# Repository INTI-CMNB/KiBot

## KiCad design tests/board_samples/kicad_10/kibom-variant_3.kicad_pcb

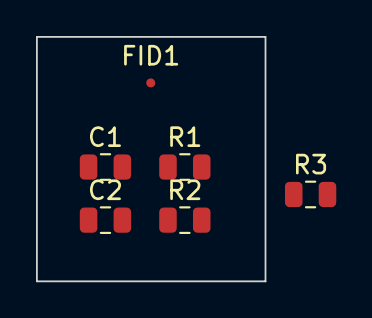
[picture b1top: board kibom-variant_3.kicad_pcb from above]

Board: 2 copper layers, 12.7 x 13.6 mm, 6 parts (0 on the bottom side), 2 nets, no tracks yet.

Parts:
C1: 1nF; C_0805_2012Metric
C2: 1000 pF; C_0805_2012Metric
FID1: Fiducial; Fiducial_0.5mm_Mask1mm
R1, R3: 1k; R_0805_2012Metric
R2: 1000; R_0805_2012Metric

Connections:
unnamed: R1.1, R3.1
unnamed: R1.2, R3.2

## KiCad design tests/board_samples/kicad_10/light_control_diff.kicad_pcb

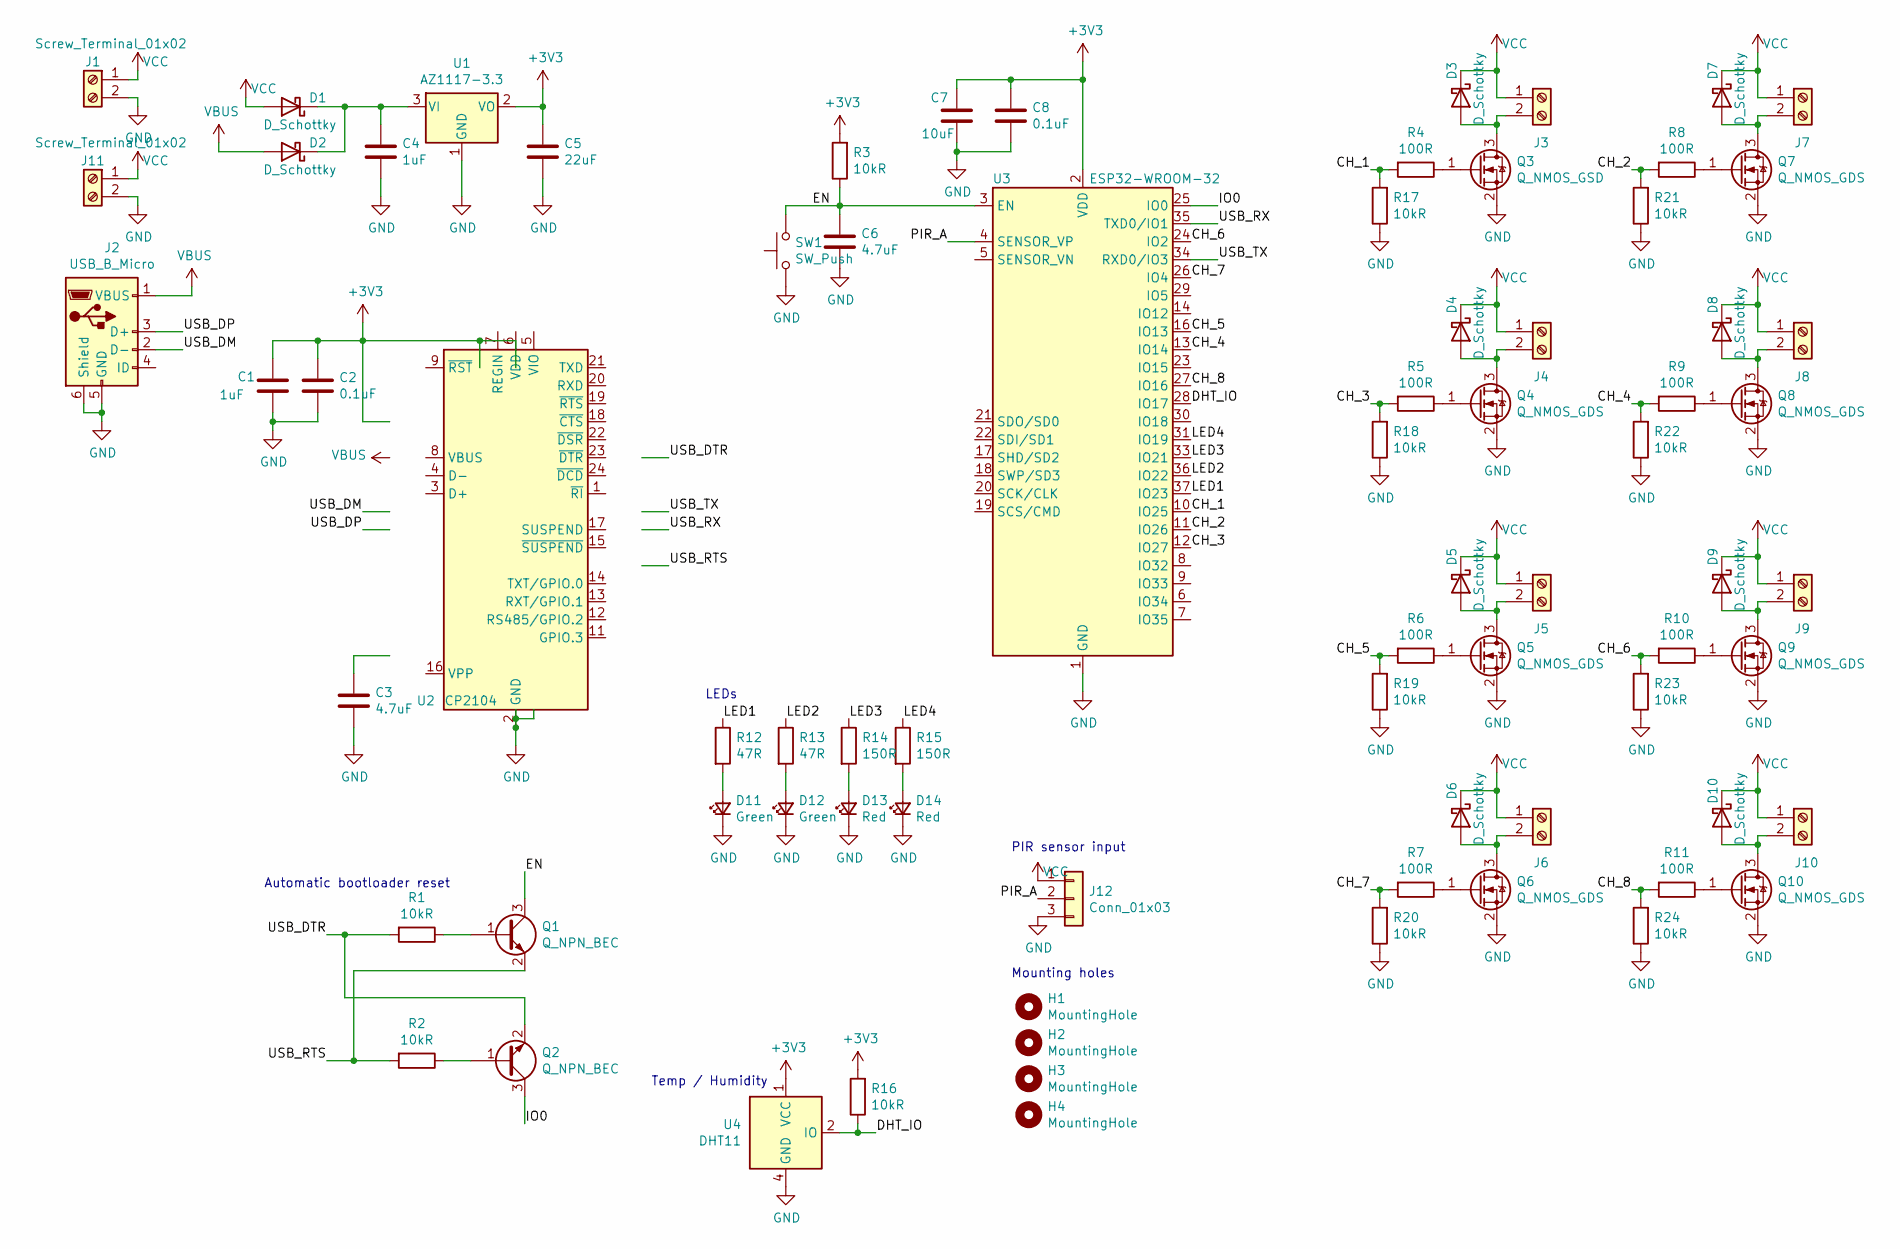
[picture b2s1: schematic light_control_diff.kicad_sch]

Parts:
C1: 1uF; R_0402_1005Metric; MPN CL05A105KA5NQNC; LCSC# C52923
C2, C8: 0.1uF; R_0402_1005Metric; MPN CL05B104KO5NNNC; LCSC# C1525
C3: 4.7uF; R_0603_1608Metric; MPN CL10A475KO8NNNC; LCSC# C19666
C4: 1uF; R_0603_1608Metric; MPN CL10A105KB8NNNC; LCSC# C15849
C5: 22uF; R_0603_1608Metric; MPN CL10A226MQ8NRNC; LCSC# C59461
C6: 4.7uF; R_0402_1005Metric; MPN CL05A475MP5NRNC; LCSC# C23733
C7: 10uF; R_0402_1005Metric; MPN CL05A106MQ5NUNC; LCSC# C15525
D1, D2, D3, D4, D5, D6, D7, D8, D9, D10: D_Schottky; D_SOD-123; MPN B5819W SL; LCSC# C8598
D11, D12: Green; LED_0603_1608Metric; MPN 19-217/GHC-YR1S2/3T; LCSC# C72043
D13, D14: Red; LED_0603_1608Metric; LCSC# C2286
H1, H2, H3, H4: MountingHole; MountingHole_3.2mm_M3
J1, J3, J4, J5, J6, J7, J8, J9, J10, J11: Screw_Terminal_01x02; TerminalBlock_Phoenix_PT-1,5-2-3.5-H_1x02_P3.50mm_Horizontal
J2: USB_B_Micro; USB_Micro-B_Molex-105017-0001
J12: Conn_01x03; JST_XH_B3B-XH-A_1x03_P2.50mm_Vertical
Q1, Q2: Q_NPN_BEC; SOT-23; MPN SS8050; LCSC# C2150
Q3: Q_NMOS_GSD; SOT-23; MPN AO3400A; LCSC# C20917
Q4, Q5, Q6, Q7, Q8, Q9, Q10: Q_NMOS_GDS; SOT-23; MPN AO3400A; LCSC# C20917
R1, R2, R3, R16, R17, R18, R19, R20, R21, R22, R23, R24: 10kR; R_0402_1005Metric; MPN 0402WGF1002TCE; LCSC# C25744
R4, R5, R6, R7, R8, R9, R10, R11: 100R; R_0402_1005Metric; MPN 0402WGF1000TCE; LCSC# C25076
R12: 47R; R_0402_1005Metric; MPN 19-217/GHC-YR1S2/3T; LCSC# C25118
R13: 47R; R_0402_1005Metric; MPN 0402WGF470JTCE; LCSC# C25118
R14, R15: 150R; R_0402_1005Metric; MPN 0402WGF1500TCE; LCSC# C25082
SW1: SW_Push; TS-1187A; MPN TS-1187A-C-D-B; LCSC# C318888
U1: AZ1117-3.3; SOT-223-3_TabPin2; MPN AZ1117CH-3.3TRG1; LCSC# C92102
U2: CP2104; QFN-24-1EP_4x4mm_P0.5mm_EP2.6x2.6mm; MPN CP2104-F03-GMR; LCSC# C47742
U3: ESP32-WROOM-32
U4: DHT11; Aosong_DHT11_5.5x12.0_P2.54mm

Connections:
+3V3: C1.1, C2.1, C5.1, C7.1, C8.1, R3.2, R16.2, U1.2 (VO), U2.5 (VIO), U2.6 (VDD), U2.7 (REGIN), U3.2 (VDD), U4.1 (VCC)
/CH_1: R4.2, R17.2, U3.10 (IO25)
/CH_2: R8.2, R21.2, U3.11 (IO26)
/CH_3: R5.2, R18.2, U3.12 (IO27)
/CH_4: R9.2, R22.2, U3.13 (IO14)
/CH_5: R6.2, R19.2, U3.16 (IO13)
/CH_6: R10.2, R23.2, U3.24 (IO2)
/CH_7: R7.2, R20.2, U3.26 (IO4)
/CH_8: R11.2, R24.2, U3.27 (IO16)
/DHT_IO: R16.1, U3.28 (IO17), U4.2 (IO)
/EN: C6.1, Q1.3 (C), R3.1, SW1.2, U3.3 (EN)
/IO0: Q2.3 (C), U3.25 (IO0)
/LED1: R12.1, U3.37 (IO23)
/LED2: R13.1, U3.36 (IO22)
/LED3: R14.1, U3.33 (IO21)
/LED4: R15.1, U3.31 (IO19)
/PIR_A: J12.2, U3.4 (SENSOR_VP)
/USB_DM: J2.2 (D-), U2.4 (D-)
/USB_DP: J2.3 (D+), U2.3 (D+)
/USB_DTR: Q2.2 (E), R1.2, U2.23 (~DTR)
/USB_RTS: Q1.2 (E), R2.2, U2.19 (~RTS)
/USB_RX: U2.20 (RXD), U3.35 (TXD0/IO1)
/USB_TX: U2.21 (TXD), U3.34 (RXD0/IO3)
GND: C1.2, C2.2, C3.2, C4.2, C5.2, C6.2, C7.2, C8.2, D11.1 (K), D12.1 (K), D13.1 (K), D14.1 (K), J1.2, J2.5 (GND), J2.6 (Shield), J11.2, J12.3, Q3.2 (S), Q4.2 (S), Q5.2 (S), Q6.2 (S), Q7.2 (S), Q8.2 (S), Q9.2 (S), Q10.2 (S), R17.1, R18.1, R19.1, R20.1, R21.1, R22.1, R23.1, R24.1, SW1.1, U1.1 (GND), U2.2 (GND), U2.25 (GND), U3.1 (GND), U3.15 (GND), U3.38 (GND), U3.39 (GND), U4.4 (GND)
unnamed: C3.1, U2.16 (VPP)
unnamed: C4.1, D1.1 (K), D2.1 (K), U1.3 (VI)
unnamed: D3.2 (A), J3.2, Q3.3 (D)
unnamed: D4.2 (A), J4.2, Q4.3 (D)
unnamed: D5.2 (A), J5.2, Q5.3 (D)
unnamed: D6.2 (A), J6.2, Q6.3 (D)
unnamed: D7.2 (A), J7.2, Q7.3 (D)
unnamed: D8.2 (A), J8.2, Q8.3 (D)
unnamed: D9.2 (A), J9.2, Q9.3 (D)
unnamed: D10.2 (A), J10.2, Q10.3 (D)
unnamed: D11.2 (A), R12.2
unnamed: D12.2 (A), R13.2
unnamed: D13.2 (A), R14.2
unnamed: D14.2 (A), R15.2
unnamed: Q1.1 (B), R1.1
unnamed: Q2.1 (B), R2.1
unnamed: Q3.1 (G), R4.1
unnamed: Q4.1 (G), R5.1
unnamed: Q5.1 (G), R6.1
unnamed: Q6.1 (G), R7.1
unnamed: Q7.1 (G), R8.1
unnamed: Q8.1 (G), R9.1
unnamed: Q9.1 (G), R10.1
unnamed: Q10.1 (G), R11.1
VBUS: D2.2 (A), J2.1 (VBUS), U2.8 (VBUS)
VCC: D1.2 (A), D3.1 (K), D4.1 (K), D5.1 (K), D6.1 (K), D7.1 (K), D8.1 (K), D9.1 (K), D10.1 (K), J1.1, J3.1, J4.1, J5.1, J6.1, J7.1, J8.1, J9.1, J10.1, J11.1, J12.1

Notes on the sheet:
PIR sensor input
Mounting holes
Temp / Humidity
LEDs
Automatic bootloader reset

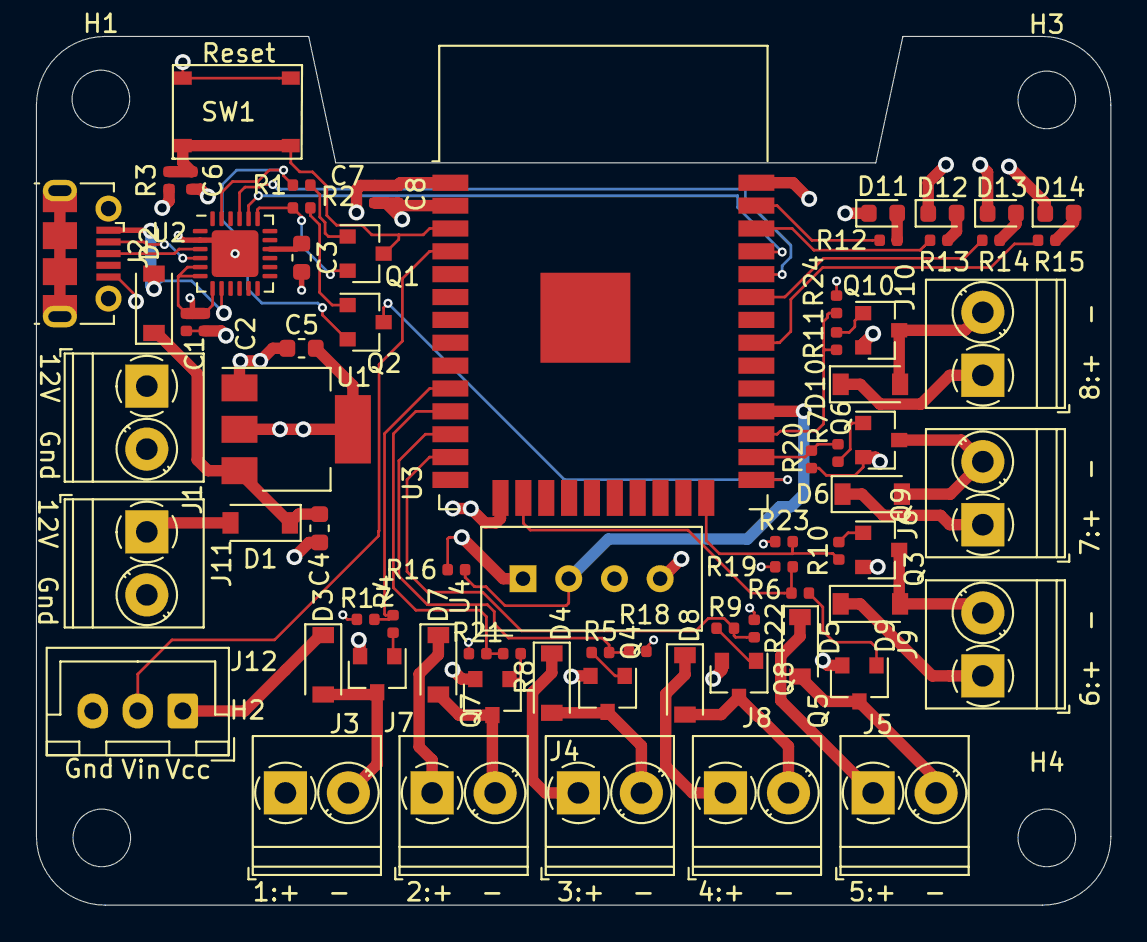
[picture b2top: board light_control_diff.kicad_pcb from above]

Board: 4 copper layers, 59.7 x 48.3 mm, 77 parts (0 on the bottom side), 50 nets.

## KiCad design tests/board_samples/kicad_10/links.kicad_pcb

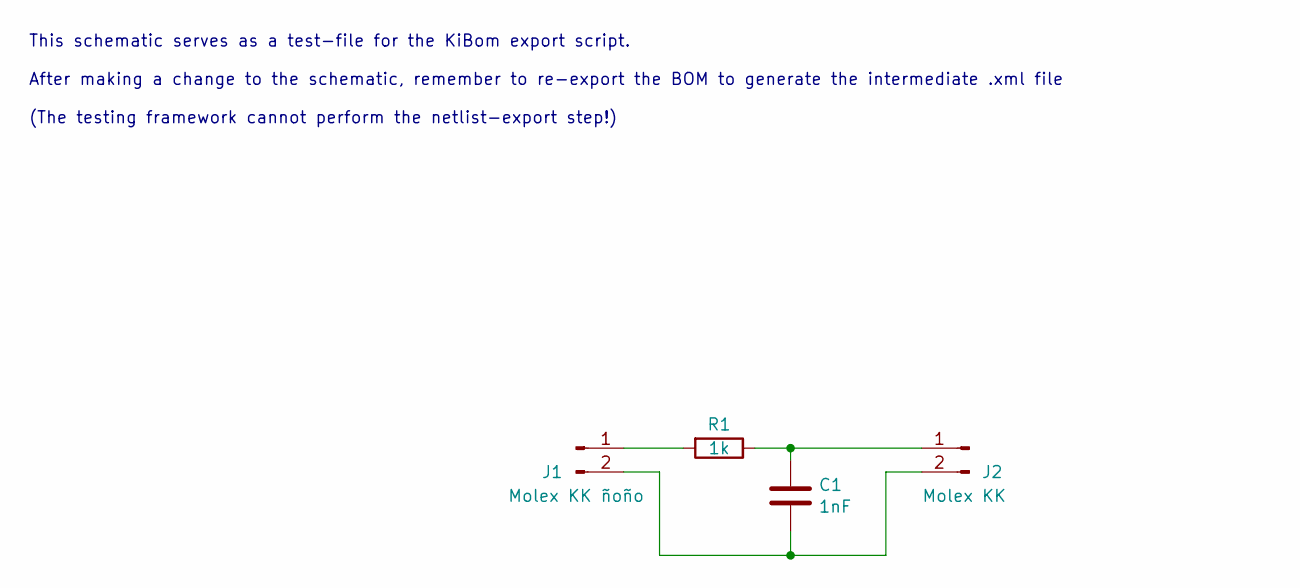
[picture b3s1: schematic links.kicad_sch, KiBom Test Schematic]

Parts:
C1: 1nF; C_0805_2012Metric; mouser# 80-C0805C102K5R; digikey# 399-1147-1-ND
J1: Molex KK ñoño; PinHeader_1x02_P2.54mm_Vertical; mouser# 538-22-23-2021; digikey# 900-0022232021-ND
J2: Molex KK; PinHeader_1x02_P2.54mm_Vertical; mouser# 538-22-23-2021; digikey# 900-0022232021-ND
R1: 1k; R_0805_2012Metric; mouser# 652-CR0805JW-102ELF; digikey# CR0805-JW-102ELFCT-ND

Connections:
unnamed: C1.1, J2.1, R1.1
unnamed: C1.2, J1.2, J2.2
unnamed: J1.1, R1.2

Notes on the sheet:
This schematic serves as a test-file for the KiBom export script. After making a change to the schematic, remember to re-export the BOM to generate the intermediate .xml file (The testing framework cannot perform the netlist-export step!)

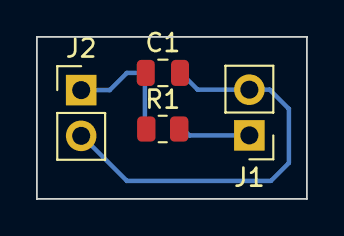
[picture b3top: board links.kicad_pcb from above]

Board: 2 copper layers, 15.0 x 9.0 mm, 4 parts (0 on the bottom side), 3 nets.
